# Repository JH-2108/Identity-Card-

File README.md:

# E-ID: Electronic Identity Card 
E-ID is a compact electronic identity card built around an ESP32-C3 microcontroller and an OLED display. It presents identity information and project details through a simple, button-controller interface. 

The project focuses on custom PCB designing in KiCAD, embedded firmware development, and practical electronics assembly. 

# Features
- Displays a name, username, role, and project information.
- Uses an OLED display with 128×64 resolution.
- Supports multiple information pages.
- Provides physical buttons for navigating the interface.
- Uses an ESP32-C3 SuperMini for processing and firmware execution.
- Connects the display and controller through a custom-designed PCB.
- Uses USB power through the development board.
- Allows identity information to be changed through firmware.

# Hardware 
| Component | Purpose | 
|---|---| 
|ESP32-C3 SuperMini | Main microcontroller | 
| 0.96 inch OLED display | Displays identity information | 
| Two tactile push buttons | Navigate between pages | 
| female pin headers | connects removable modules | 
| Custom two-layer PCB | Holds and connects the components | 

# How it works 
The ESP32-C3 runs the firmware and communicates with the OLED display. The display presents the current information page, while the physical buttons allow the user to switch between pages. 

The initial firmware will provide three pages: 
1. **Identity**: Name, username, and role.
2. **About**: A short biography or introduction.
3. **Projects**: Selected projects and technical interests.

The information will initially be stored in the firmware, so changing the displayed content will require updating and uploading the code. 

# PCB Design 
The PCB will be designed in KiCAD and will include: 
- A footprint and header connections for the ESP32-C3 SuperMini.
- A four pin OLED connector
- Two-button footprints
- Power and ground connections
- Routing between the controller, display, and buttons.
- A compact board outline inspired by the dimensions of a standard identity card.

The development board and OLED will remain removable, allowing individual components to be replaced without redesigning the entire PCB. 

The PCB layout will be finalized after checking the actual dimensions and pin positions of the selected modules. 

# Firmware 
The firmware will be developed  using the Arduino framework for the ESP32-C3. 

Planned software functions include: 
- Initializing the OLED display.
- Rendering text and page layouts.
- reading button inputs.
- switching between information pages.
- displaying a consistent interface after setup.

The SSD1306 compatible display library will be used if the selected OLED module supports the SSD1306 controller. 

# Images of the project 

**PCB design** 

**schematics** 

**3D Rendering**

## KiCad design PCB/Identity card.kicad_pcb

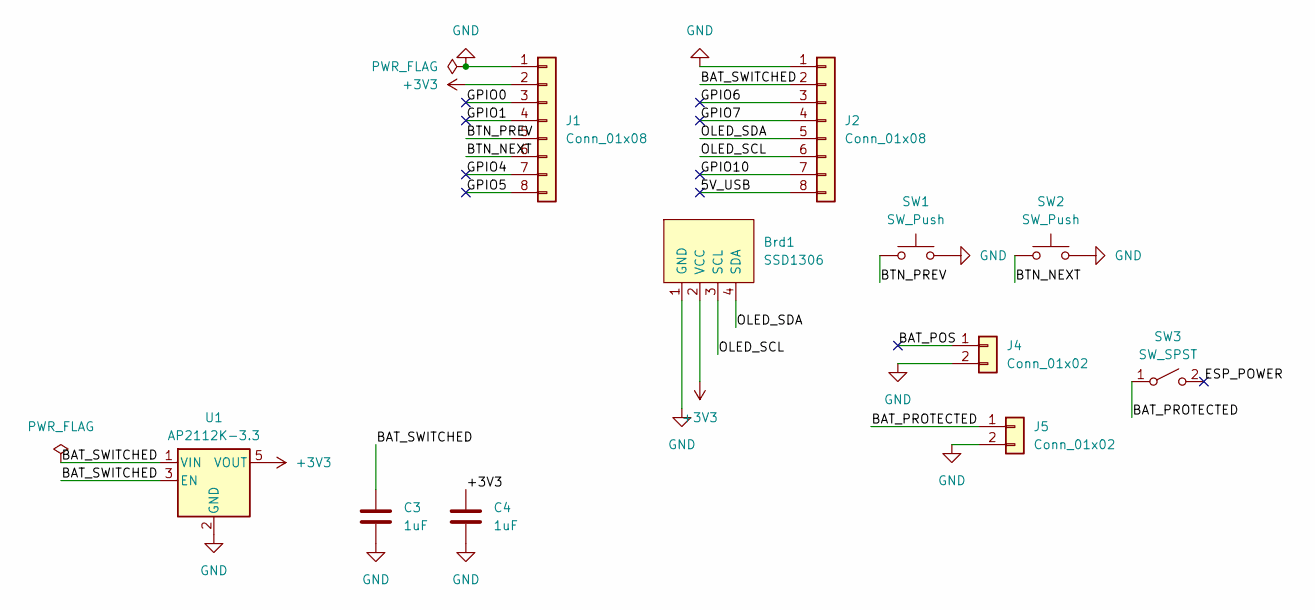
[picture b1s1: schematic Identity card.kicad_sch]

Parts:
Brd1: SSD1306; 128x64OLED
C3, C4: 1uF; C_0805_2012Metric
J1, J2: Conn_01x08; PinHeader_1x08_P2.54mm_Vertical
J4: Conn_01x02; JST_PH_B2B-PH-K_1x02_P2.00mm_Vertical
J5: Conn_01x02; PinHeader_1x02_P2.54mm_Vertical
SW1, SW2: SW_Push; SW_PUSH_6mm
SW3: SW_SPST; SW_SPST_Omron_B3F-40xx
U1: AP2112K-3.3; SOT-23-5

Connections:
+3V3: Brd1.2 (VCC), C4.1, J1.2, U1.5 (VOUT)
/5V_USB: J2.8
/BAT_POS: J4.1
/BAT_PROTECTED: J5.1, SW3.1 (A)
/BAT_SWITCHED: C3.1, J2.2, U1.1 (VIN), U1.3 (EN)
/BTN_NEXT: J1.6, SW2.1
/BTN_PREV: J1.5, SW1.1
/ESP_POWER: SW3.2 (B)
/ESP_POWER_1: SW3.2 (B)
/GPIO0: J1.3
/GPIO1: J1.4
/GPIO4: J1.7
/GPIO5: J1.8
/GPIO6: J2.3
/GPIO7: J2.4
/GPIO10: J2.7
/OLED_SCL: Brd1.3 (SCL), J2.6
/OLED_SDA: Brd1.4 (SDA), J2.5
GND: Brd1.1 (GND), C3.2, C4.2, J1.1, J2.1, J4.2, J5.2, SW1.2, SW2.2, U1.2 (GND)

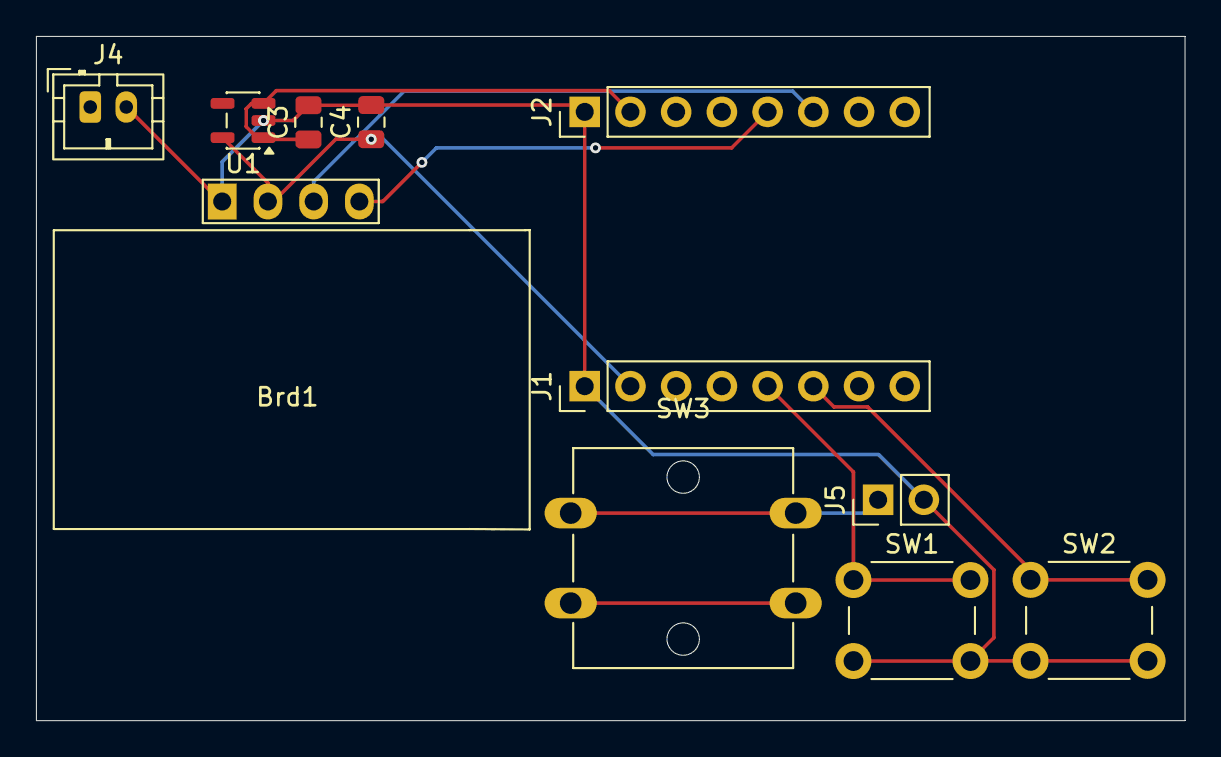
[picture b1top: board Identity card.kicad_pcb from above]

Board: 2 copper layers, 63.8 x 38.0 mm, 11 parts (0 on the bottom side), 8 nets.
